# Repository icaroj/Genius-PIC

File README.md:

# Jogo de Memória com PIC

Projeto baseado no jogo _Color Memory_ - no Brasil conhecido como Genius - utilizando um PIC 16F628A.

Código em C (Compialdor Microchip XC8) e PCB projetada no Kicad. 

# PCB

- 4 Leds coloridos
- 4 Botões de jogo + START/RESET
- Barramento para o PICKIT 3
- Bateria 9V
- Resistores
- Buzzer
- LM 7805
- PIC

# TODO:

- Gerar os beeps

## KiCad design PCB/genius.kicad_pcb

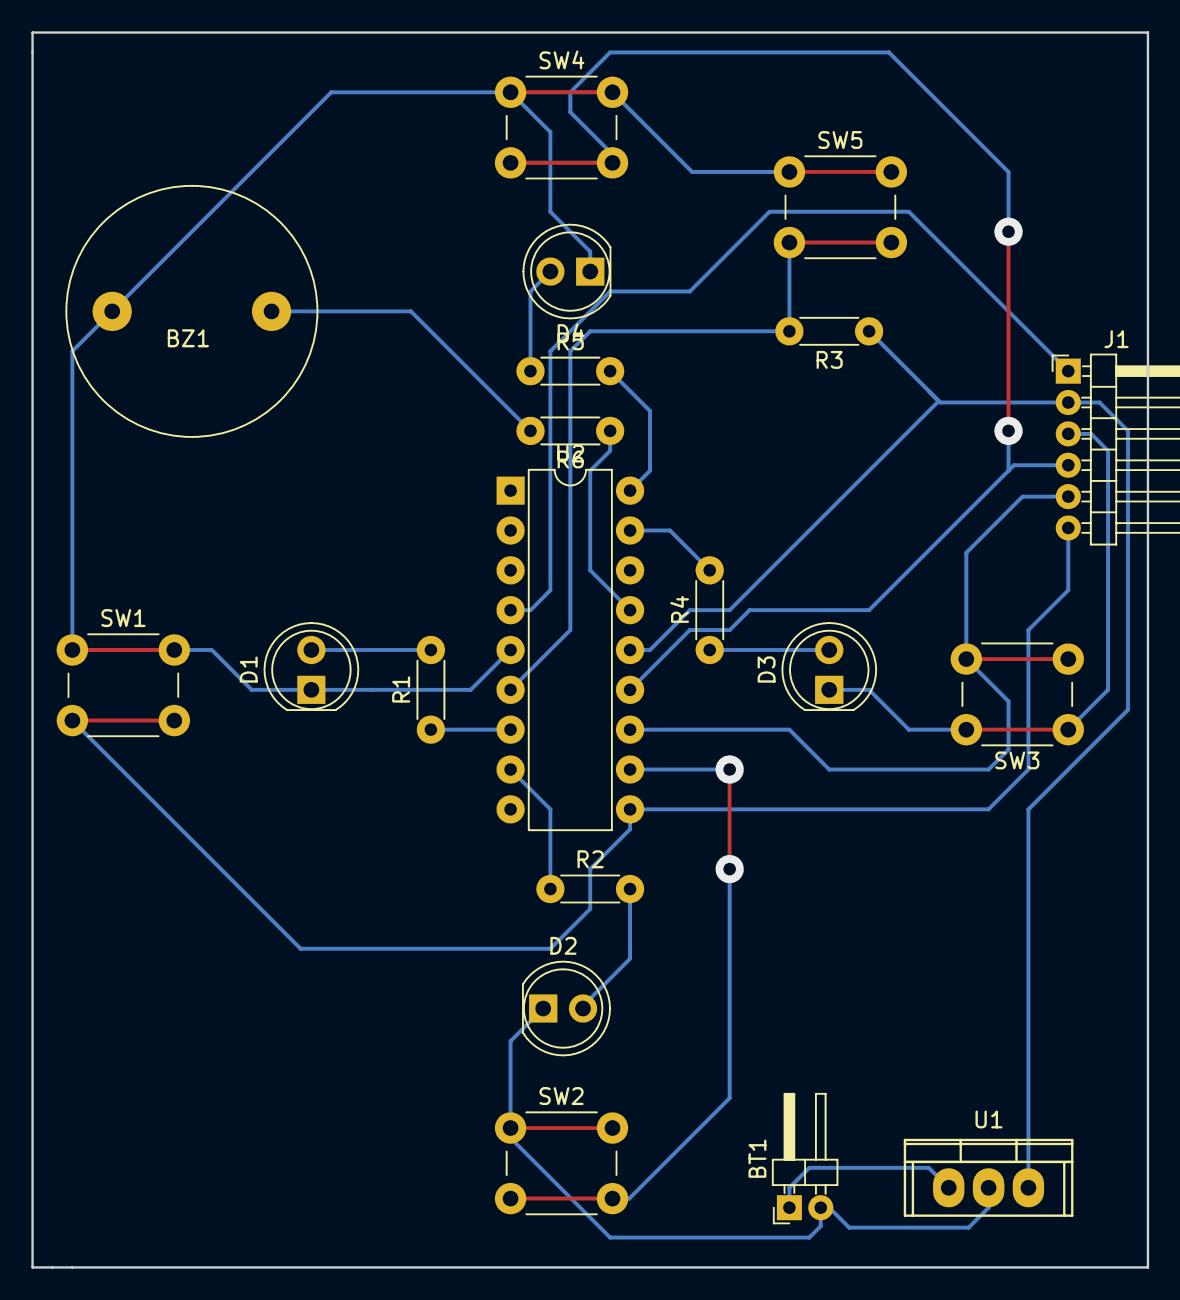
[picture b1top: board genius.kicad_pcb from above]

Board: 2 copper layers, 71.1 x 78.7 mm, 20 parts (0 on the bottom side), 19 nets.

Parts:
BT1: Battery; Pin_Header_Angled_1x02_Pitch2.00mm
BZ1: Buzzer; BUZZER
D1, D2, D3, D4: LED; LED_D5.0mm
J1: PICKIT3_CONN; Pin_Header_Angled_1x06_Pitch2.00mm
R1, R2, R4, R5: 220; R_Axial_DIN0204_L3.6mm_D1.6mm_P5.08mm_Horizontal
R3: 6k8; R_Axial_DIN0204_L3.6mm_D1.6mm_P5.08mm_Horizontal
R6: 100; R_Axial_DIN0204_L3.6mm_D1.6mm_P5.08mm_Horizontal
SW1, SW2, SW3, SW4, SW5: SW_Push; SW_PUSH_6mm
U1: L7805; TO-220
U2: PIC16(L)F628A-I/P; DIP-18_W7.62mm

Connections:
/MCLR: J1.1, U2.4
/PGC: J1.5, SW3.2, U2.12
/PGD: J1.4, SW4.2, U2.13
/PGM: J1.6, SW1.2, U2.10
GND: BT1.2, BZ1.2, D1.1, D2.1, D3.1, D4.1, J1.3, SW1.1, SW2.1, SW3.1, SW4.1, SW5.1, U1.2, U2.5
unnamed: BT1.1, U1.1
unnamed: BZ1.1, R6.2
unnamed: D1.2, R1.2
unnamed: D2.2, R2.2
unnamed: D3.2, R4.1
unnamed: D4.2, R5.1
unnamed: R1.1, U2.7
unnamed: R2.1, U2.8
unnamed: R3.2, SW5.2, U2.6
unnamed: R4.2, U2.17
unnamed: R5.2, U2.18
unnamed: R6.1, U2.15
unnamed: SW2.2, U2.11
VCC: J1.2, R3.1, U1.3, U2.14

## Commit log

2017-10-02 Botoes adicionados
2017-10-03 Com botoes funcionando e algumas partes comentadas por causa dos testes...
2017-10-03 Jogo praticamente pronto com botoes, sequencia aleatoria e botao reset. Falta o buzzer/beeps.
2017-10-06 sem som por enquanto...
2017-10-06 sem som.
2017-10-06 READ me melhorado
2017-10-12 Rev. PCB
